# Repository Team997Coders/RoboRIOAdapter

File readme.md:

# RoboRIOAdapter

This project has moved! See https://github.com/Team997Coders/997-hardware for updates on this PCB and others.

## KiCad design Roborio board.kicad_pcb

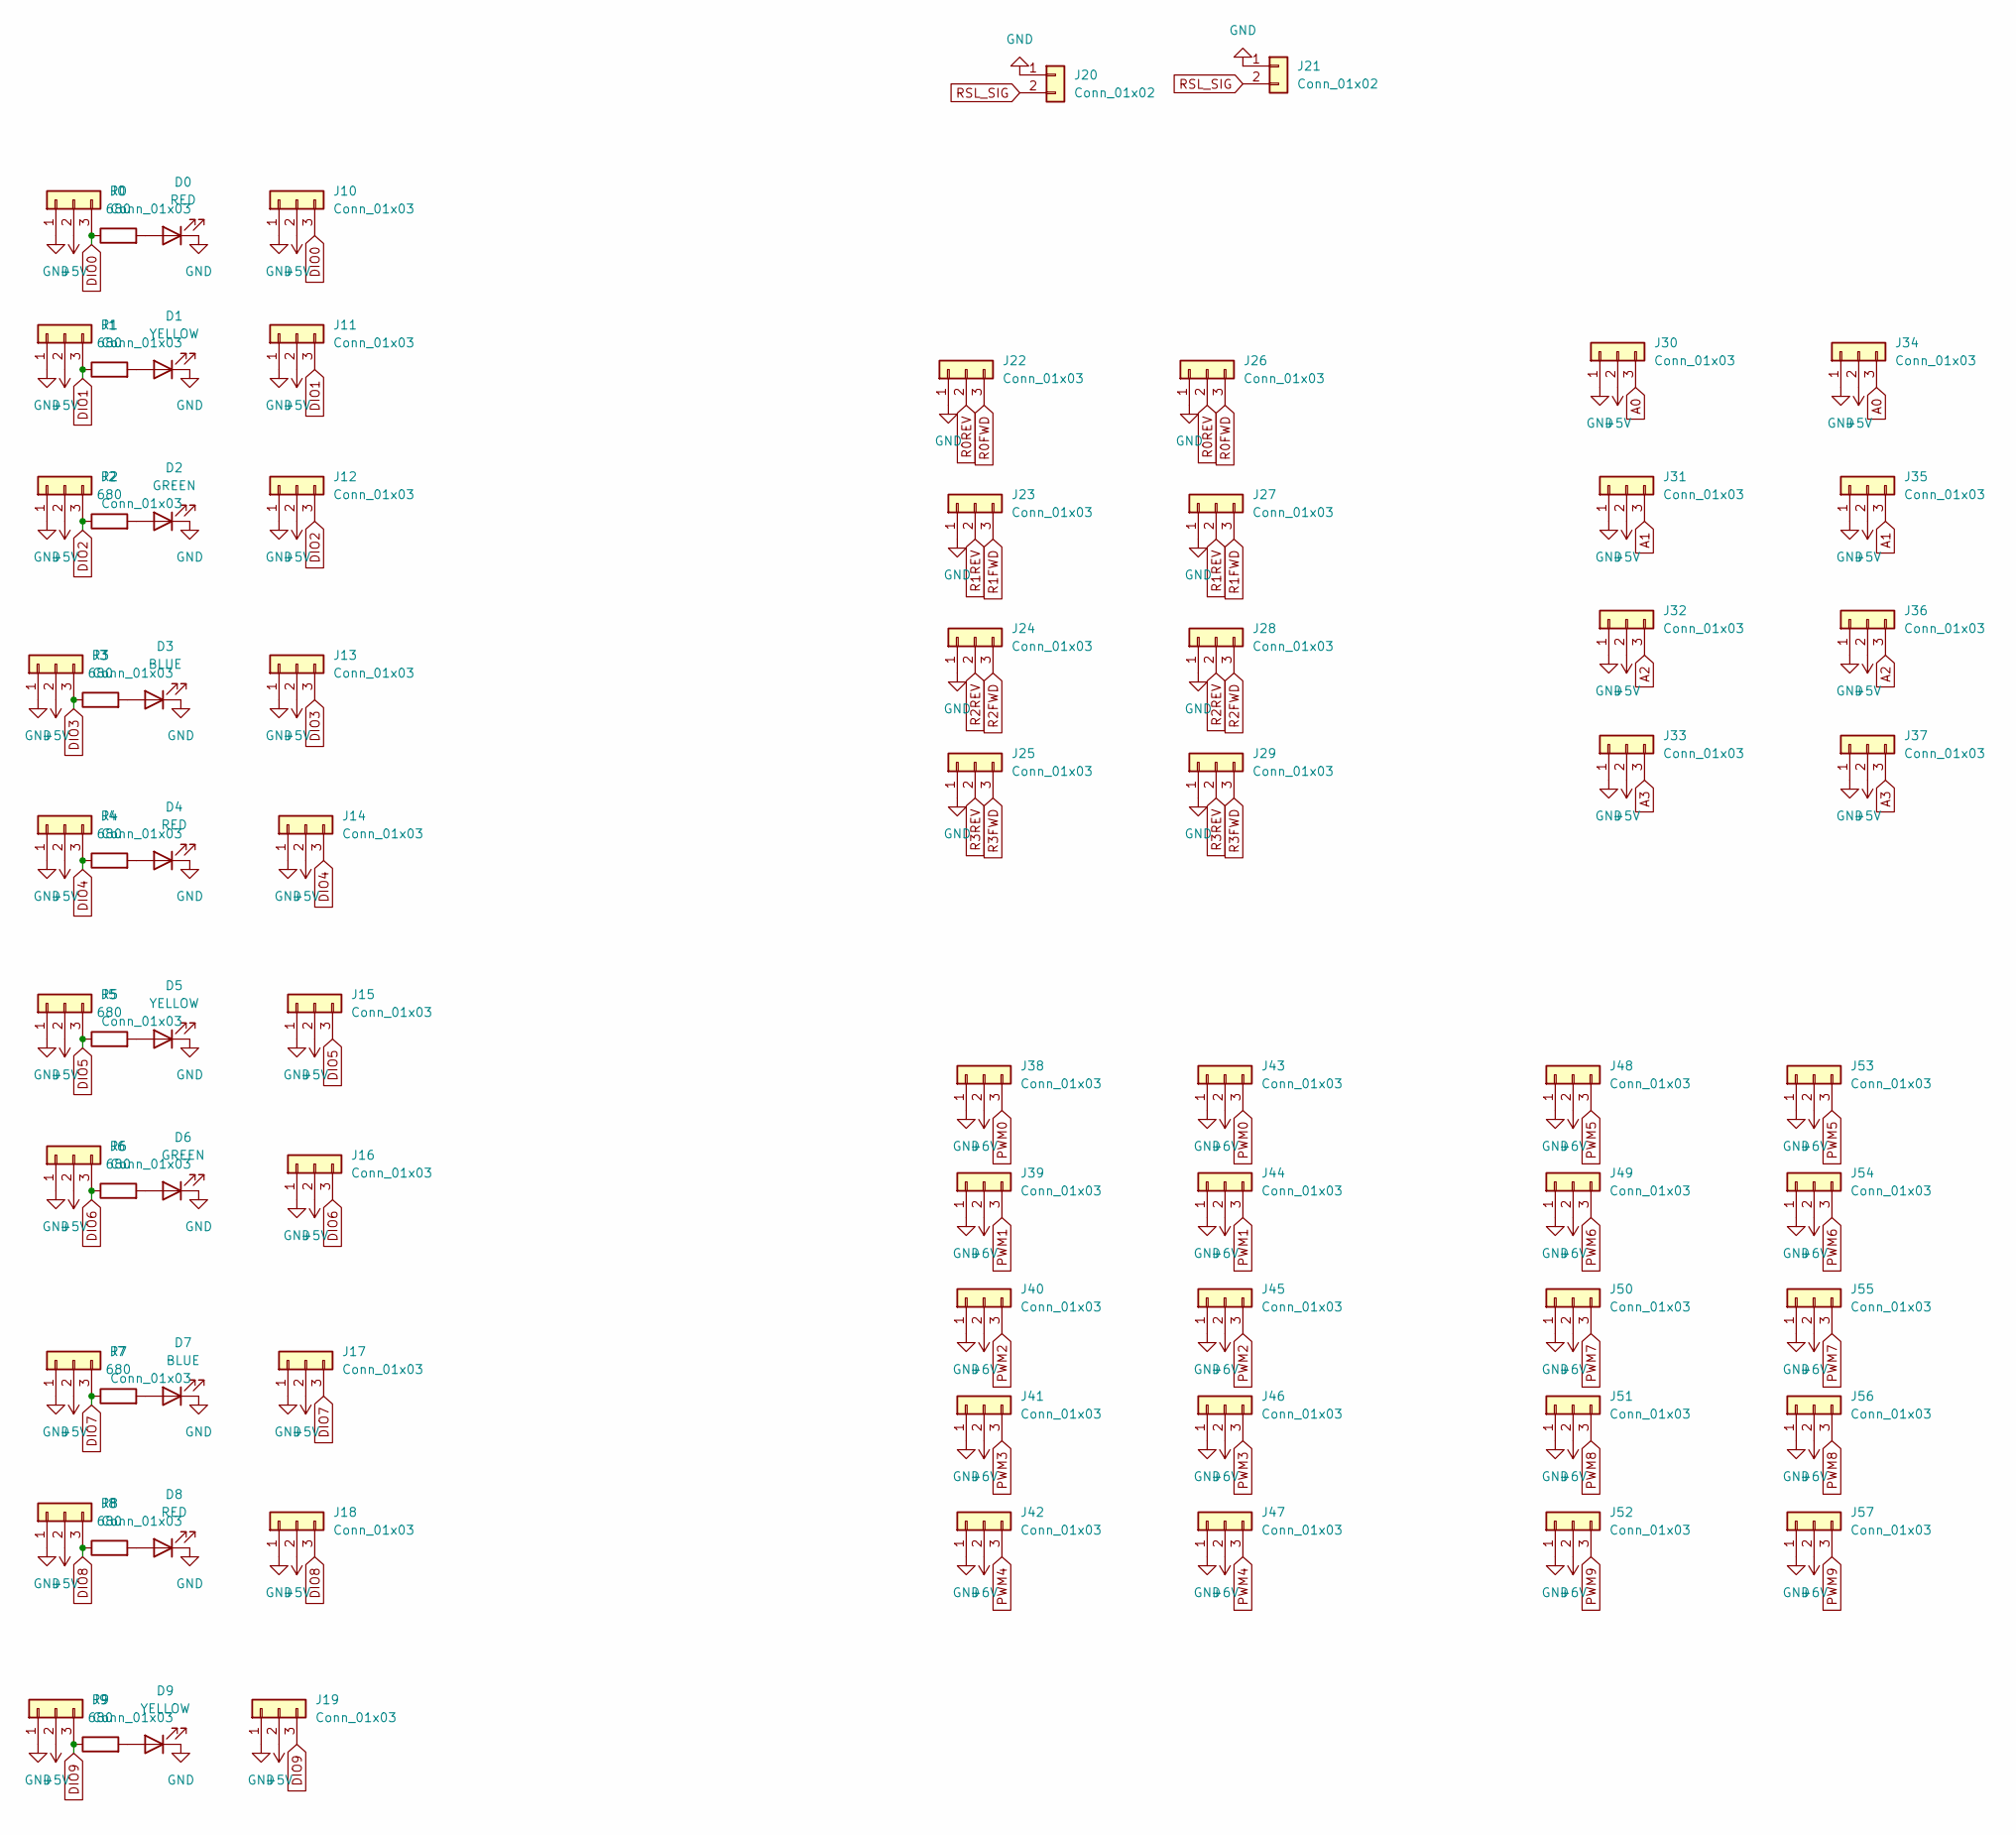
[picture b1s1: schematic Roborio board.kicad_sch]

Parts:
D0, D4, D8: RED; LED_0603_1608Metric
D1, D5, D9: YELLOW; LED_0603_1608Metric
D2, D6: GREEN; LED_0603_1608Metric
D3, D7: BLUE; LED_0603_1608Metric
J0, J1, J2, J3, J4, J5, J6, J7, J8, J9, J22, J23, J24, J25, J30, J31, J32, J33, J38, J39, J40, J41, J42, J48, J49, J50, J51, J52: Conn_01x03; PinSocket_1x03_P2.54mm_Vertical
J10, J11, J12, J13, J14, J15, J16, J17, J18, J19, J26, J27, J28, J29, J34, J35, J36, J37, J43, J44, J45, J46, J47, J53, J54, J55, J56, J57: Conn_01x03; JST_XH_B3B-XH-A_1x03_P2.50mm_Vertical
J20: Conn_01x02; PinSocket_1x02_P2.54mm_Vertical
J21: Conn_01x02; JST_XH_B2B-XH-A_1x02_P2.50mm_Vertical
R0, R1, R2, R3, R4, R5, R6, R7, R8, R9: 680; R_0603_1608Metric

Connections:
+5V: J0.2, J1.2, J2.2, J3.2, J4.2, J5.2, J6.2, J7.2, J8.2, J9.2, J10.2, J11.2, J12.2, J13.2, J14.2, J15.2, J16.2, J17.2, J18.2, J19.2, J30.2, J31.2, J32.2, J33.2, J34.2, J35.2, J36.2, J37.2
+6V: J38.2, J39.2, J40.2, J41.2, J42.2, J43.2, J44.2, J45.2, J46.2, J47.2, J48.2, J49.2, J50.2, J51.2, J52.2, J53.2, J54.2, J55.2, J56.2, J57.2
A0: J30.3, J34.3
A1: J31.3, J35.3
A2: J32.3, J36.3
A3: J33.3, J37.3
DIO0: J0.3, J10.3, R0.1
DIO1: J1.3, J11.3, R1.1
DIO2: J2.3, J12.3, R2.1
DIO3: J3.3, J13.3, R3.1
DIO4: J4.3, J14.3, R4.1
DIO5: J5.3, J15.3, R5.1
DIO6: J6.3, J16.3, R6.1
DIO7: J7.3, J17.3, R7.1
DIO8: J8.3, J18.3, R8.1
DIO9: J9.3, J19.3, R9.1
GND: D0.1 (K), D1.1 (K), D2.1 (K), D3.1 (K), D4.1 (K), D5.1 (K), D6.1 (K), D7.1 (K), D8.1 (K), D9.1 (K), J0.1, J1.1, J2.1, J3.1, J4.1, J5.1, J6.1, J7.1, J8.1, J9.1, J10.1, J11.1, J12.1, J13.1, J14.1, J15.1, J16.1, J17.1, J18.1, J19.1, J20.1, J21.1, J22.1, J23.1, J24.1, J25.1, J26.1, J27.1, J28.1, J29.1, J30.1, J31.1, J32.1, J33.1, J34.1, J35.1, J36.1, J37.1, J38.1, J39.1, J40.1, J41.1, J42.1, J43.1, J44.1, J45.1, J46.1, J47.1, J48.1, J49.1, J50.1, J51.1, J52.1, J53.1, J54.1, J55.1, J56.1, J57.1
unnamed: D0.2 (A), R0.2
unnamed: D1.2 (A), R1.2
unnamed: D2.2 (A), R2.2
unnamed: D3.2 (A), R3.2
unnamed: D4.2 (A), R4.2
unnamed: D5.2 (A), R5.2
unnamed: D6.2 (A), R6.2
unnamed: D7.2 (A), R7.2
unnamed: D8.2 (A), R8.2
unnamed: D9.2 (A), R9.2
PWM0: J38.3, J43.3
PWM1: J39.3, J44.3
PWM2: J40.3, J45.3
PWM3: J41.3, J46.3
PWM4: J42.3, J47.3
PWM5: J48.3, J53.3
PWM6: J49.3, J54.3
PWM7: J50.3, J55.3
PWM8: J51.3, J56.3
PWM9: J52.3, J57.3
R0FWD: J22.3, J26.3
R0REV: J22.2, J26.2
R1FWD: J23.3, J27.3
R1REV: J23.2, J27.2
R2FWD: J24.3, J28.3
R2REV: J24.2, J28.2
R3FWD: J25.3, J29.3
R3REV: J25.2, J29.2
RSL_SIG: J20.2, J21.2

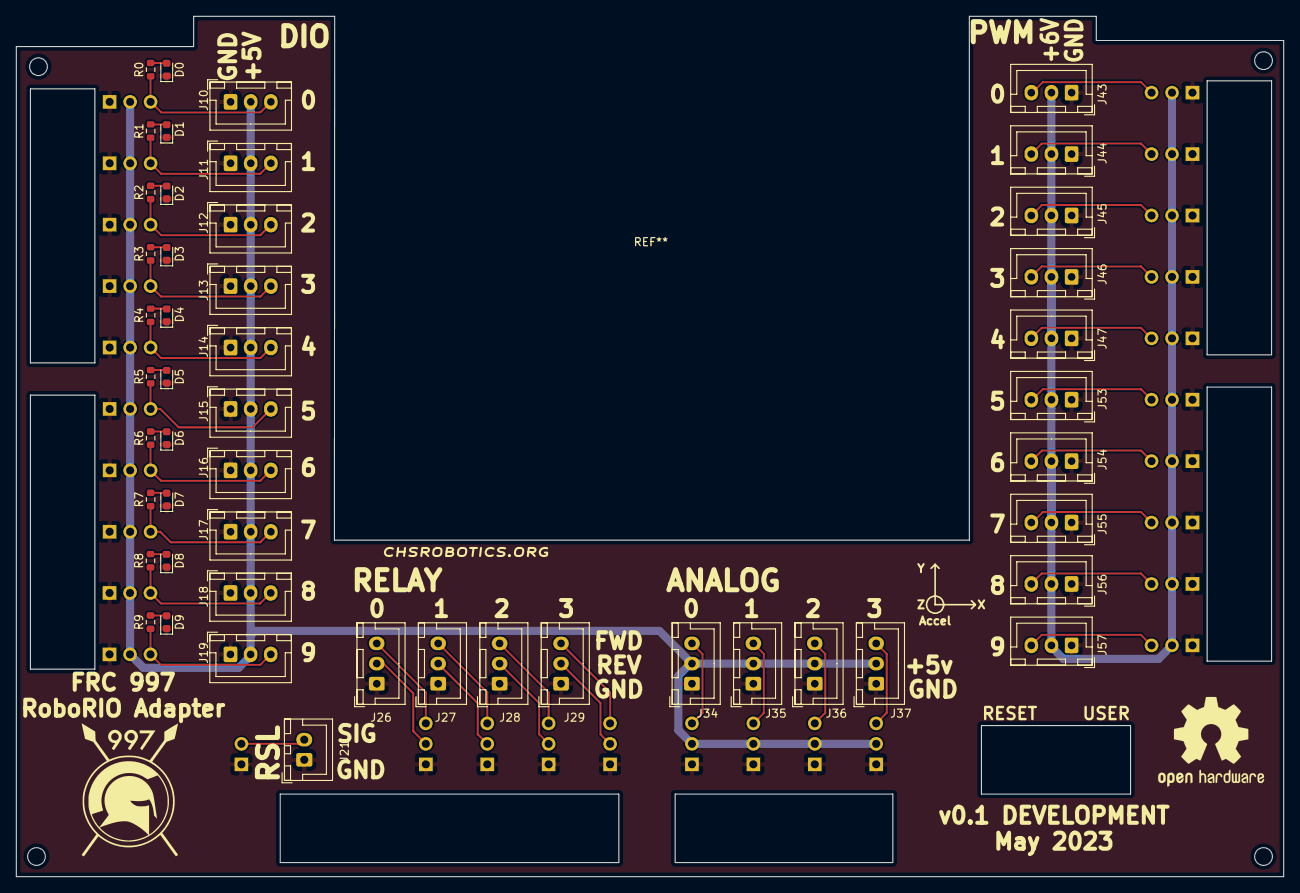
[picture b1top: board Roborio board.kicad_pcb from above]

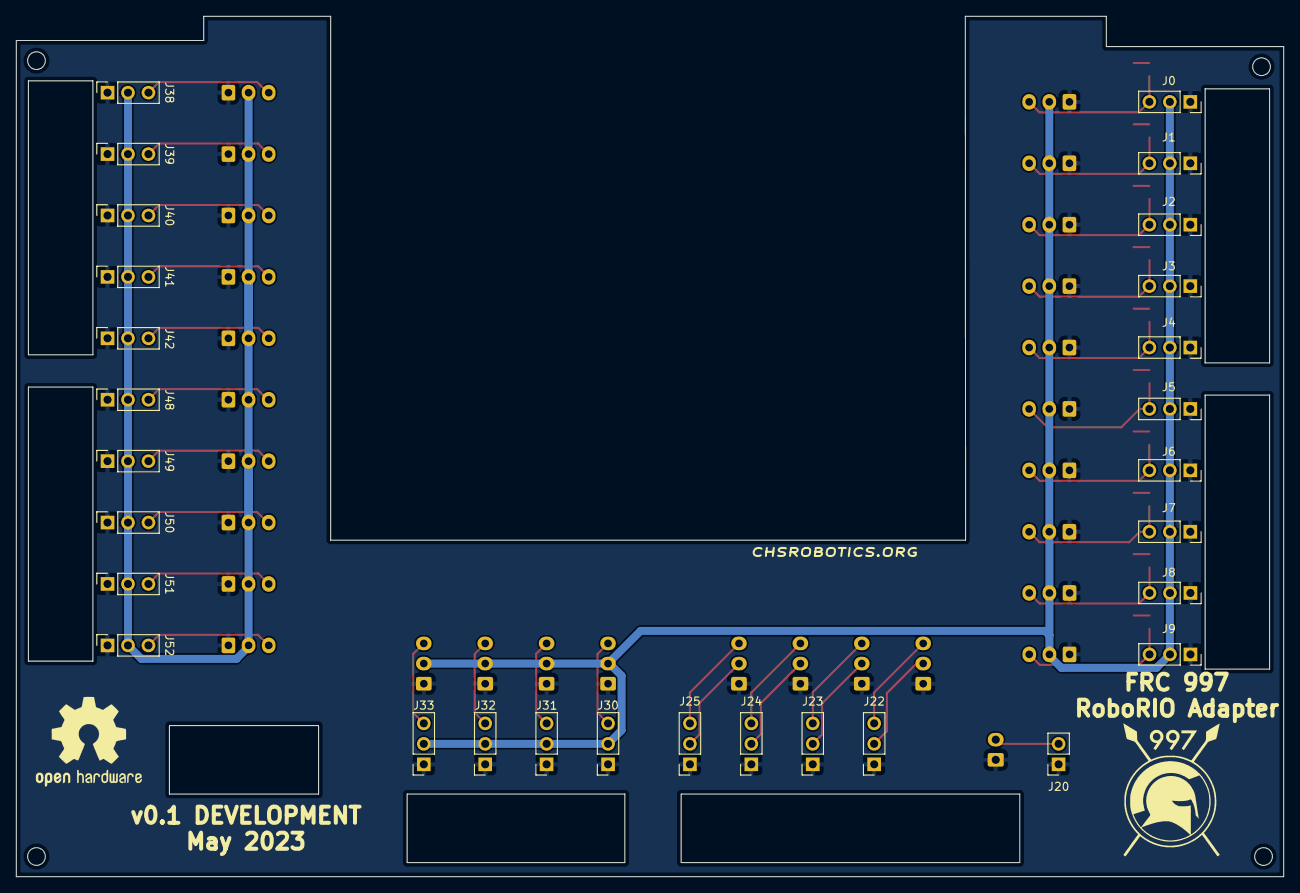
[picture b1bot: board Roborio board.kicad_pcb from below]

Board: 2 copper layers, 157.2 x 106.8 mm, 78 parts (29 on the bottom side), 46 nets.

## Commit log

2023-05-13 Initial commit of RoboRIO breakout PCB project
2023-05-13 Add image to readme
2023-08-04 Point to new repo
